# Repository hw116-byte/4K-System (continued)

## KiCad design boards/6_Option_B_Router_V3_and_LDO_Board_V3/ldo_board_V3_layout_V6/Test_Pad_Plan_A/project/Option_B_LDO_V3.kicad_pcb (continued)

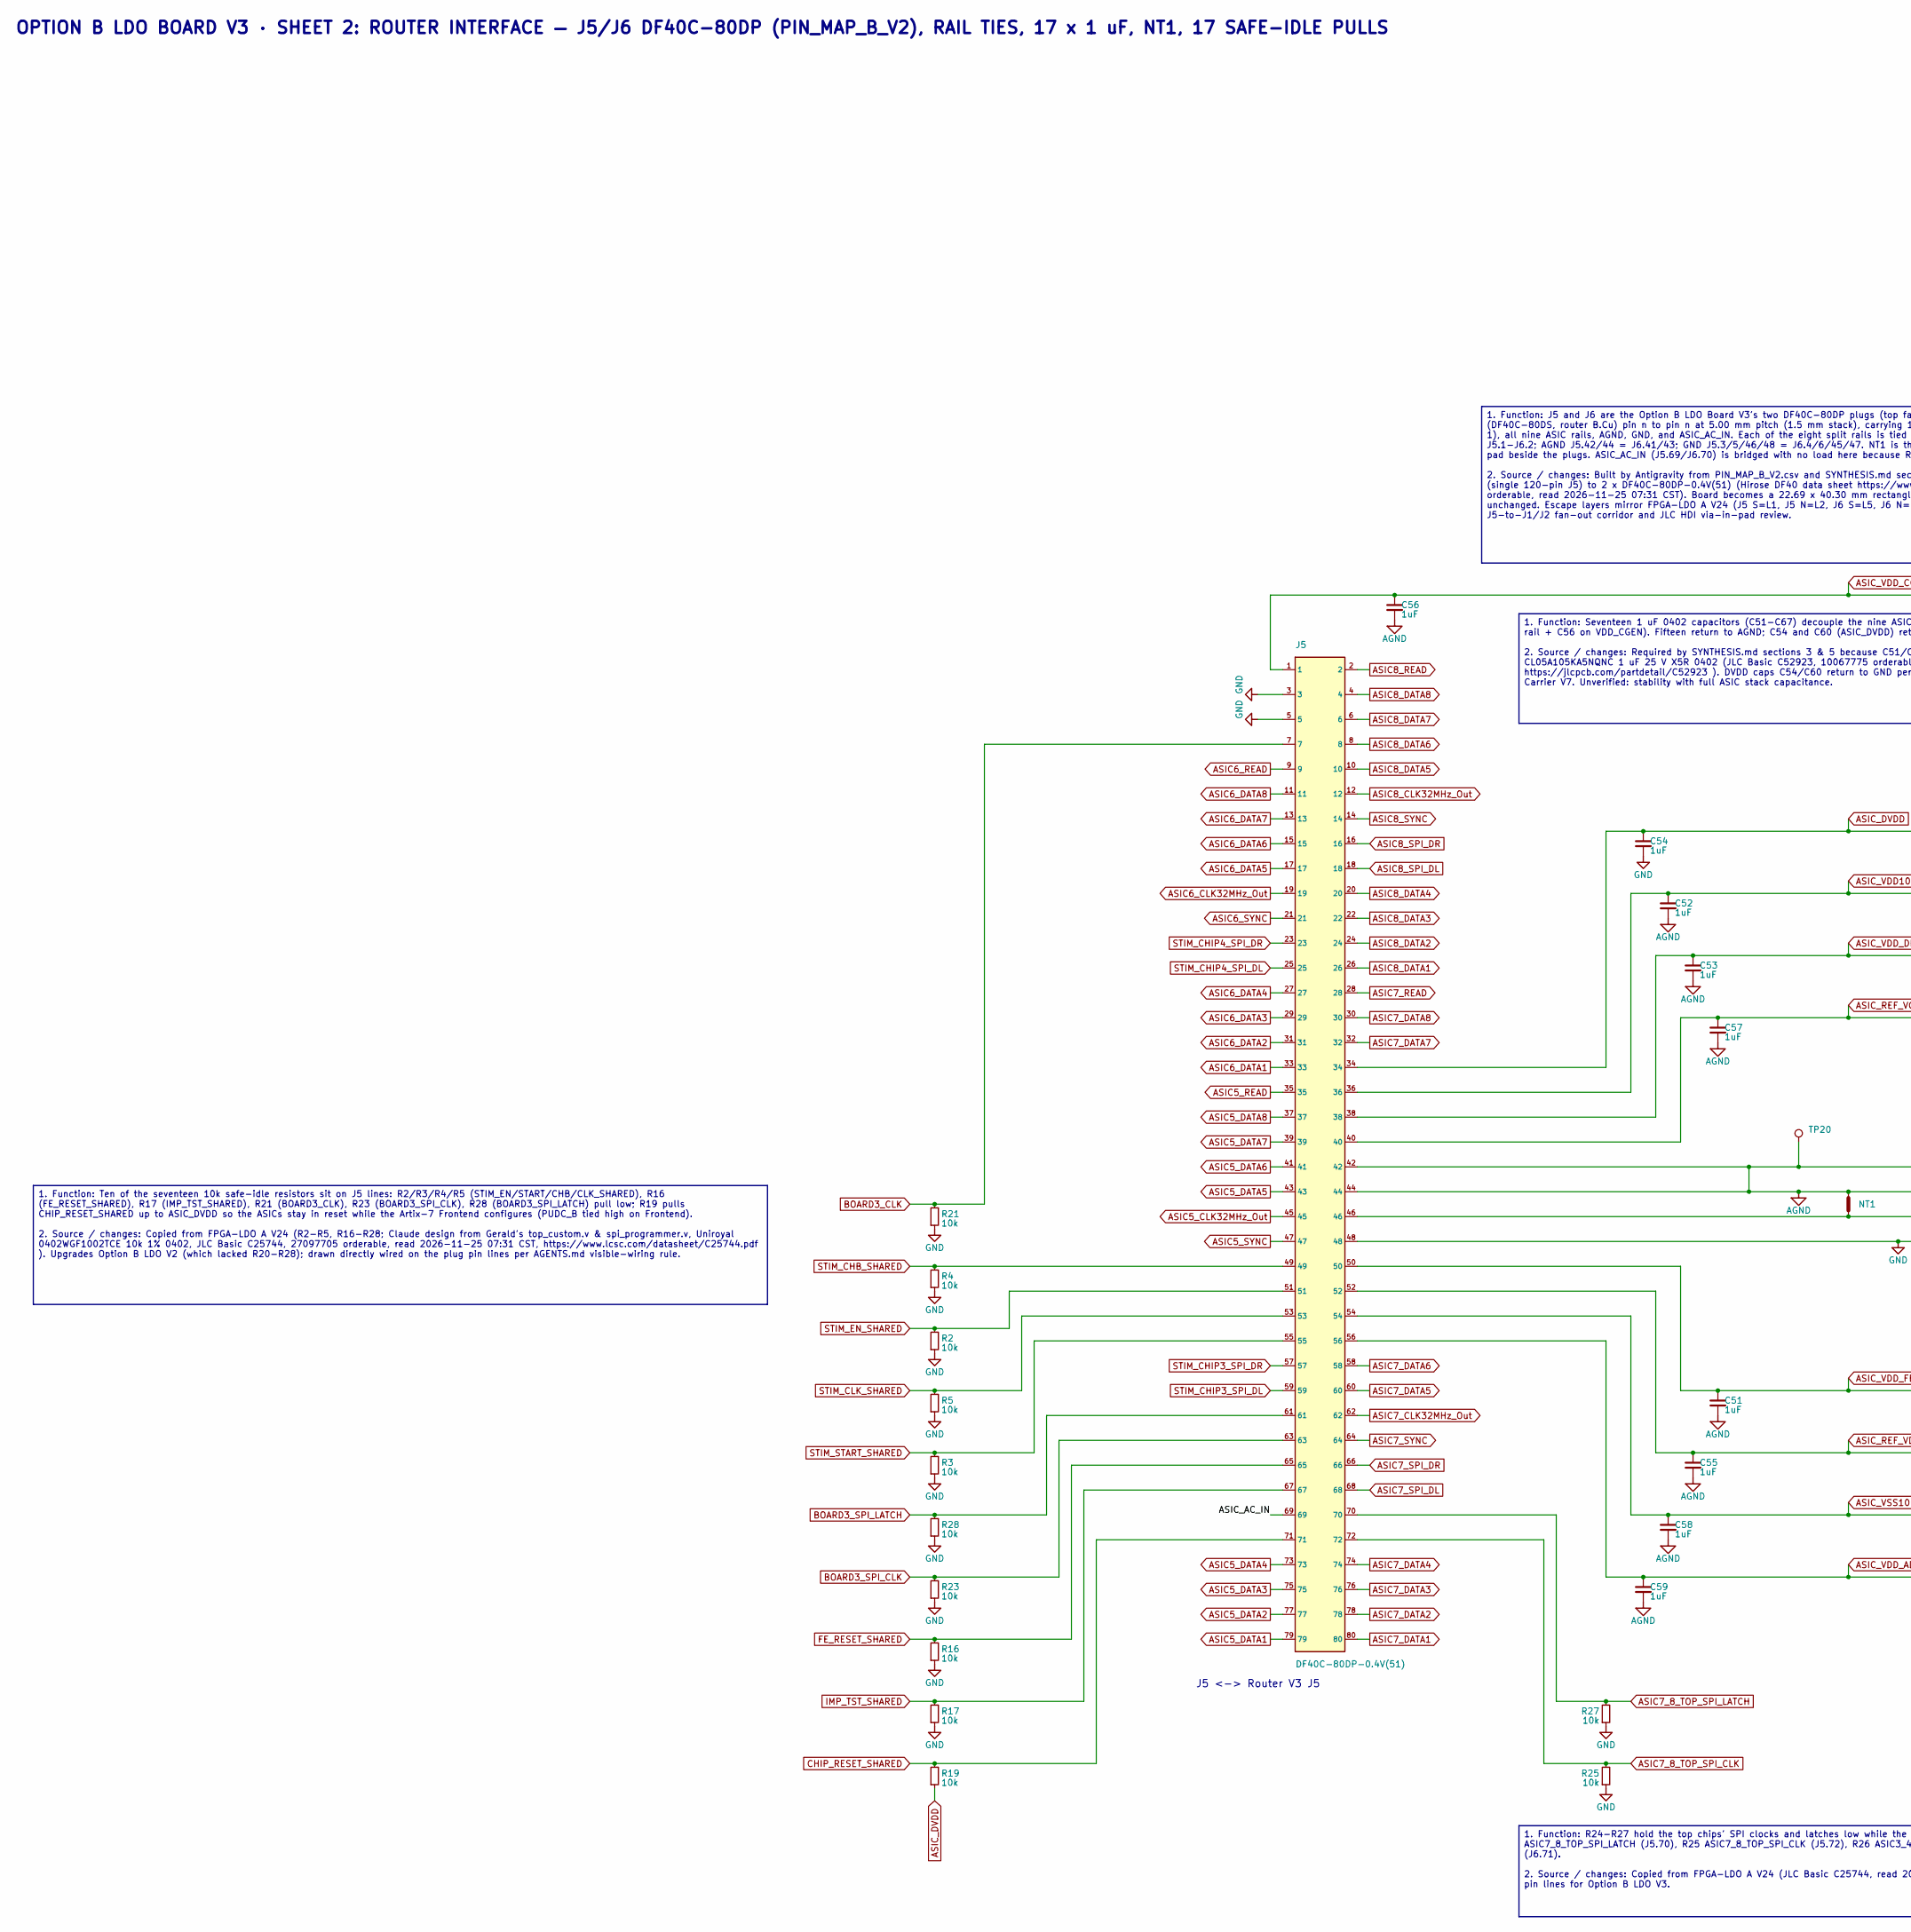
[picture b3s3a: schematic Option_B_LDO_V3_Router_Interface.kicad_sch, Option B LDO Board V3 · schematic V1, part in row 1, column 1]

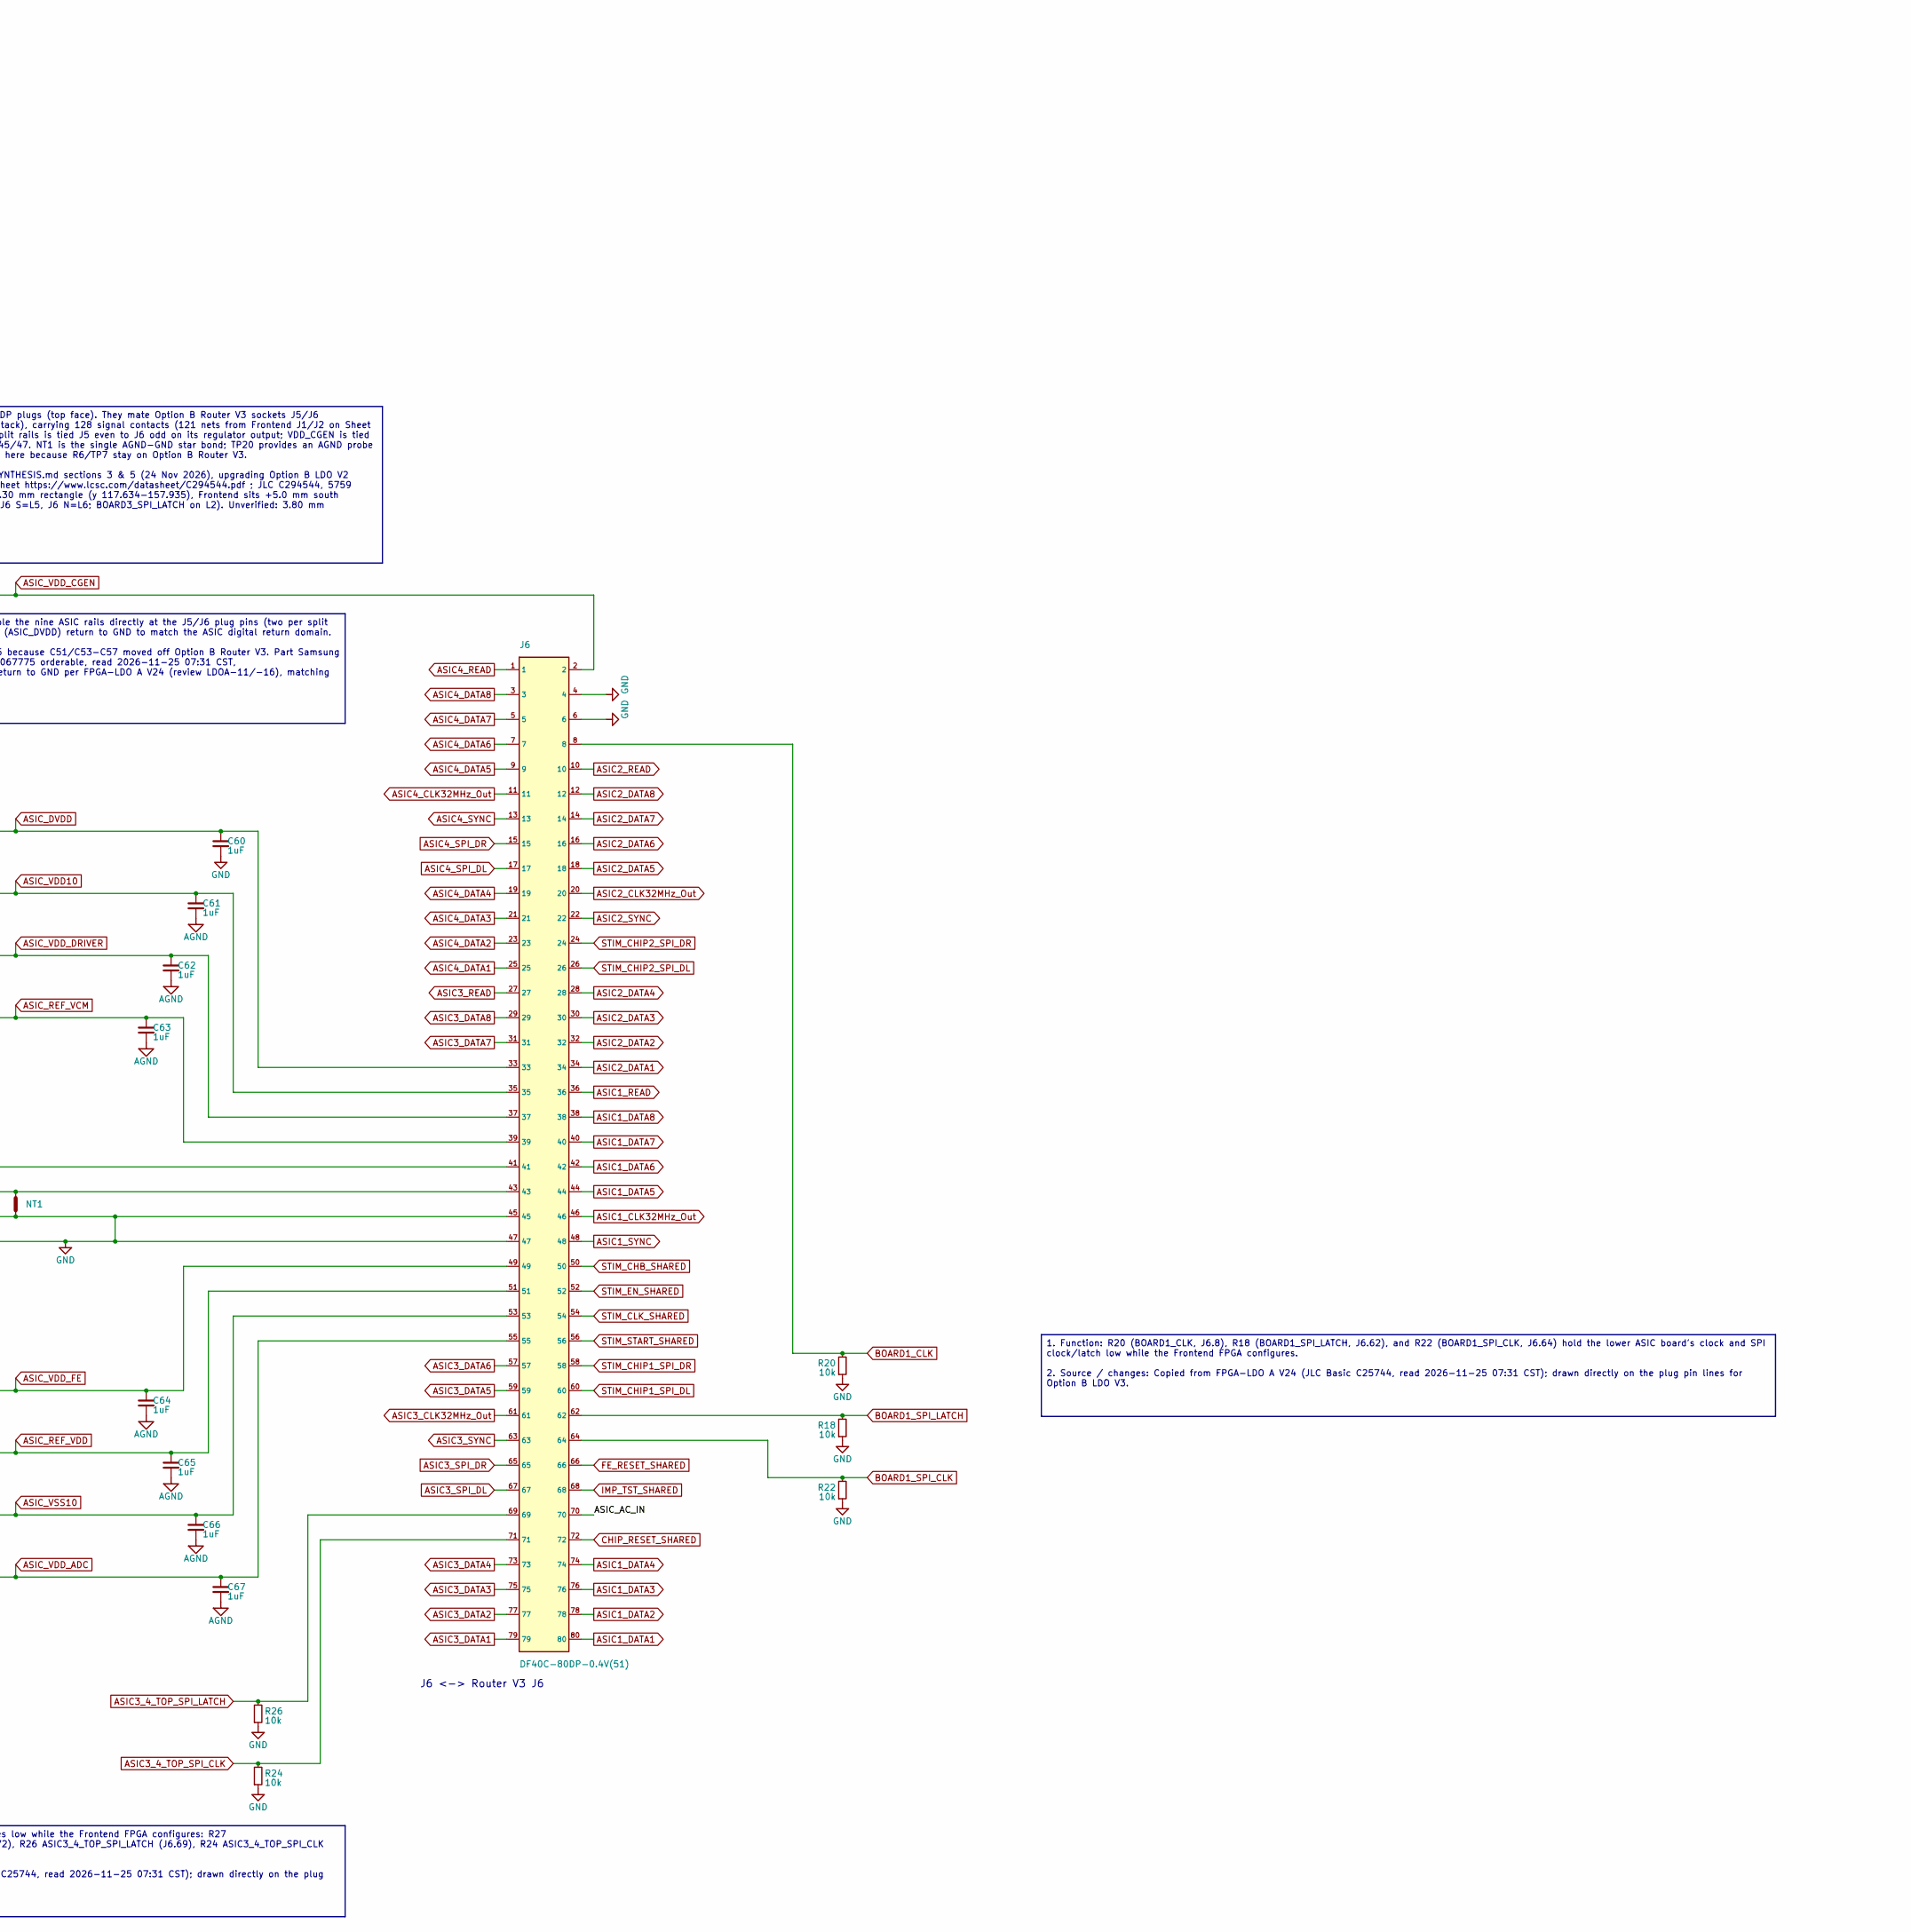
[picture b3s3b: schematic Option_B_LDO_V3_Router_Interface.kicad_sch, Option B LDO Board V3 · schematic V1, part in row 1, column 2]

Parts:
C51, C52, C53, C54, C55, C56, C57, C58, C59, C60, C61, C62, C63, C64, C65, C66, C67: 1uF; C_0402_1005Metric; Voltage 25V; MPN Samsung CL05A105KA5NQNC (1 uF 25 V X5R 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; LCSC C52923
J5, J6: DF40C-80DP-0.4V(51); Hirose_DF40C-80DP-0.4V_2x40-1MP_P0.4mm; MPN DF40C-80DP-0.4V(51); LCSC C294544
NT1: NetTie_2; NetTie-2_SMD_Pad0.5mm
R2, R3, R4, R5, R16, R17, R18, R19, R20, R21, R22, R23, R24, R25, R26, R27, R28: 10k; R_0402_1005Metric; MPN Uniroyal 0402WGF1002TCE (10k 1% 0402); LCSC C25744
TP20: AGND; TestPoint_Pad_D1.0mm_Compact

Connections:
/Router_Interface/ASIC_AC_IN: J5.69, J6.70
AGND: C51.2, C52.2, C53.2, C55.2, C56.2, C57.2, C58.2, C59.2, C61.2, C62.2, C63.2, C64.2, C65.2, C66.2, C67.2, J5.42, J5.44, J6.41, J6.43, NT1.2, TP20.1; also elsewhere on the board
ASIC1_CLK32MHz_Out: J6.46; also elsewhere on the board
ASIC1_DATA1: J6.80; also elsewhere on the board
ASIC1_DATA2: J6.78; also elsewhere on the board
ASIC1_DATA3: J6.76; also elsewhere on the board
ASIC1_DATA4: J6.74; also elsewhere on the board
ASIC1_DATA5: J6.44; also elsewhere on the board
ASIC1_DATA6: J6.42; also elsewhere on the board
ASIC1_DATA7: J6.40; also elsewhere on the board
ASIC1_DATA8: J6.38; also elsewhere on the board
ASIC1_READ: J6.36; also elsewhere on the board
ASIC1_SYNC: J6.48; also elsewhere on the board
ASIC2_CLK32MHz_Out: J6.20; also elsewhere on the board
ASIC2_DATA1: J6.34; also elsewhere on the board
ASIC2_DATA2: J6.32; also elsewhere on the board
ASIC2_DATA3: J6.30; also elsewhere on the board
ASIC2_DATA4: J6.28; also elsewhere on the board
ASIC2_DATA5: J6.18; also elsewhere on the board
ASIC2_DATA6: J6.16; also elsewhere on the board
ASIC2_DATA7: J6.14; also elsewhere on the board
ASIC2_DATA8: J6.12; also elsewhere on the board
ASIC2_READ: J6.10; also elsewhere on the board
ASIC2_SYNC: J6.22; also elsewhere on the board
ASIC3_4_TOP_SPI_CLK: J6.71, R24.1; also elsewhere on the board
ASIC3_4_TOP_SPI_LATCH: J6.69, R26.1; also elsewhere on the board
ASIC3_CLK32MHz_Out: J6.61; also elsewhere on the board
ASIC3_DATA1: J6.79; also elsewhere on the board
ASIC3_DATA2: J6.77; also elsewhere on the board
ASIC3_DATA3: J6.75; also elsewhere on the board
ASIC3_DATA4: J6.73; also elsewhere on the board
ASIC3_DATA5: J6.59; also elsewhere on the board
ASIC3_DATA6: J6.57; also elsewhere on the board
ASIC3_DATA7: J6.31; also elsewhere on the board
ASIC3_DATA8: J6.29; also elsewhere on the board
ASIC3_READ: J6.27; also elsewhere on the board
ASIC3_SPI_DL: J6.67; also elsewhere on the board
ASIC3_SPI_DR: J6.65; also elsewhere on the board
ASIC3_SYNC: J6.63; also elsewhere on the board
ASIC4_CLK32MHz_Out: J6.11; also elsewhere on the board
ASIC4_DATA1: J6.25; also elsewhere on the board
ASIC4_DATA2: J6.23; also elsewhere on the board
ASIC4_DATA3: J6.21; also elsewhere on the board
ASIC4_DATA4: J6.19; also elsewhere on the board
ASIC4_DATA5: J6.9; also elsewhere on the board
ASIC4_DATA6: J6.7; also elsewhere on the board
ASIC4_DATA7: J6.5; also elsewhere on the board
ASIC4_DATA8: J6.3; also elsewhere on the board
ASIC4_READ: J6.1; also elsewhere on the board
ASIC4_SPI_DL: J6.17; also elsewhere on the board
ASIC4_SPI_DR: J6.15; also elsewhere on the board
ASIC4_SYNC: J6.13; also elsewhere on the board
ASIC5_CLK32MHz_Out: J5.45; also elsewhere on the board
ASIC5_DATA1: J5.79; also elsewhere on the board
ASIC5_DATA2: J5.77; also elsewhere on the board
ASIC5_DATA3: J5.75; also elsewhere on the board
ASIC5_DATA4: J5.73; also elsewhere on the board
ASIC5_DATA5: J5.43; also elsewhere on the board
ASIC5_DATA6: J5.41; also elsewhere on the board
ASIC5_DATA7: J5.39; also elsewhere on the board
ASIC5_DATA8: J5.37; also elsewhere on the board
ASIC5_READ: J5.35; also elsewhere on the board
ASIC5_SYNC: J5.47; also elsewhere on the board
ASIC6_CLK32MHz_Out: J5.19; also elsewhere on the board
ASIC6_DATA1: J5.33; also elsewhere on the board
ASIC6_DATA2: J5.31; also elsewhere on the board
ASIC6_DATA3: J5.29; also elsewhere on the board
ASIC6_DATA4: J5.27; also elsewhere on the board
ASIC6_DATA5: J5.17; also elsewhere on the board
ASIC6_DATA6: J5.15; also elsewhere on the board
ASIC6_DATA7: J5.13; also elsewhere on the board
ASIC6_DATA8: J5.11; also elsewhere on the board
ASIC6_READ: J5.9; also elsewhere on the board
ASIC6_SYNC: J5.21; also elsewhere on the board
ASIC7_8_TOP_SPI_CLK: J5.72, R25.1; also elsewhere on the board
ASIC7_8_TOP_SPI_LATCH: J5.70, R27.1; also elsewhere on the board
ASIC7_CLK32MHz_Out: J5.62; also elsewhere on the board
ASIC7_DATA1: J5.80; also elsewhere on the board
ASIC7_DATA2: J5.78; also elsewhere on the board
ASIC7_DATA3: J5.76; also elsewhere on the board
ASIC7_DATA4: J5.74; also elsewhere on the board
ASIC7_DATA5: J5.60; also elsewhere on the board
ASIC7_DATA6: J5.58; also elsewhere on the board
ASIC7_DATA7: J5.32; also elsewhere on the board
ASIC7_DATA8: J5.30; also elsewhere on the board
ASIC7_READ: J5.28; also elsewhere on the board
ASIC7_SPI_DL: J5.68; also elsewhere on the board
ASIC7_SPI_DR: J5.66; also elsewhere on the board
ASIC7_SYNC: J5.64; also elsewhere on the board
ASIC8_CLK32MHz_Out: J5.12; also elsewhere on the board
ASIC8_DATA1: J5.26; also elsewhere on the board
ASIC8_DATA2: J5.24; also elsewhere on the board
ASIC8_DATA3: J5.22; also elsewhere on the board
ASIC8_DATA4: J5.20; also elsewhere on the board
ASIC8_DATA5: J5.10; also elsewhere on the board
ASIC8_DATA6: J5.8; also elsewhere on the board
ASIC8_DATA7: J5.6; also elsewhere on the board
ASIC8_DATA8: J5.4; also elsewhere on the board
ASIC8_READ: J5.2; also elsewhere on the board
ASIC8_SPI_DL: J5.18; also elsewhere on the board
ASIC8_SPI_DR: J5.16; also elsewhere on the board
ASIC8_SYNC: J5.14; also elsewhere on the board
ASIC_DVDD: C54.1, C60.1, J5.34, J6.33, R19.2; also elsewhere on the board
ASIC_REF_VCM: C57.1, C63.1, J5.40, J6.39; also elsewhere on the board
ASIC_REF_VDD: C55.1, C65.1, J5.52, J6.51; also elsewhere on the board
ASIC_VDD10: C52.1, C61.1, J5.36, J6.35; also elsewhere on the board
ASIC_VDD_ADC: C59.1, C67.1, J5.56, J6.55; also elsewhere on the board
ASIC_VDD_CGEN: C56.1, J5.1, J6.2; also elsewhere on the board
ASIC_VDD_DRIVER: C53.1, C62.1, J5.38, J6.37; also elsewhere on the board
ASIC_VDD_FE: C51.1, C64.1, J5.50, J6.49; also elsewhere on the board
ASIC_VSS10: C58.1, C66.1, J5.54, J6.53; also elsewhere on the board
BOARD1_CLK: J6.8, R20.1; also elsewhere on the board
BOARD1_SPI_CLK: J6.64, R22.1; also elsewhere on the board
BOARD1_SPI_LATCH: J6.62, R18.1; also elsewhere on the board
BOARD3_CLK: J5.7, R21.1; also elsewhere on the board
BOARD3_SPI_CLK: J5.63, R23.1; also elsewhere on the board
BOARD3_SPI_LATCH: J5.61, R28.1; also elsewhere on the board
CHIP_RESET_SHARED: J5.71, J6.72, R19.1; also elsewhere on the board
FE_RESET_SHARED: J5.65, J6.66, R16.1; also elsewhere on the board
GND: C54.2, C60.2, J5.3, J5.5, J5.46, J5.48, J6.4, J6.6, J6.45, J6.47, NT1.1, R2.2, R3.2, R4.2, R5.2, R16.2, R17.2, R18.2, R20.2, R21.2, R22.2, R23.2, R24.2, R25.2, R26.2, R27.2, R28.2; also elsewhere on the board
IMP_TST_SHARED: J5.67, J6.68, R17.1; also elsewhere on the board
STIM_CHB_SHARED: J5.49, J6.50, R4.1; also elsewhere on the board
STIM_CHIP1_SPI_DL: J6.60; also elsewhere on the board
STIM_CHIP1_SPI_DR: J6.58; also elsewhere on the board
STIM_CHIP2_SPI_DL: J6.26; also elsewhere on the board
STIM_CHIP2_SPI_DR: J6.24; also elsewhere on the board
STIM_CHIP3_SPI_DL: J5.59; also elsewhere on the board
STIM_CHIP3_SPI_DR: J5.57; also elsewhere on the board
STIM_CHIP4_SPI_DL: J5.25; also elsewhere on the board
STIM_CHIP4_SPI_DR: J5.23; also elsewhere on the board
STIM_CLK_SHARED: J5.53, J6.54, R5.1; also elsewhere on the board
STIM_EN_SHARED: J5.51, J6.52, R2.1; also elsewhere on the board
STIM_START_SHARED: J5.55, J6.56, R3.1; also elsewhere on the board

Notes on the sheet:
1. Function: J5 and J6 are the Option B LDO Board V3's two DF40C-80DP plugs (top face). They mate Option B Router V3 sockets J5/J6 (DF40C-80DS, router B.Cu) pin n to pin n at 5.00 mm pitch (1.5 mm stack), carrying 128 signal contacts (121 nets from Frontend J1/J2 on Sheet 1), all nine ASIC rails, A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
1. Function: Seventeen 1 uF 0402 capacitors (C51-C67) decouple the nine ASIC rails directly at the J5/J6 plug pins (two per split rail + C56 on VDD_CGEN). Fifteen return to AGND; C54 and C60 (ASIC_DVDD) return to GND to match the ASIC digital return domain. 2. Source / changes: Required by SYNTHESI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
1. Function: Ten of the seventeen 10k safe-idle resistors sit on J5 lines: R2/R3/R4/R5 (STIM_EN/START/CHB/CLK_SHARED), R16 (FE_RESET_SHARED), R17 (IMP_TST_SHARED), R21 (BOARD3_CLK), R23 (BOARD3_SPI_CLK), R28 (BOARD3_SPI_LATCH) pull low; R19 pulls CHIP_RESET_SHARED up to ASIC_DVDD so the ASICs stay 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
1. Function: R24-R27 hold the top chips' SPI clocks and latches low while the Frontend FPGA configures: R27 ASIC7_8_TOP_SPI_LATCH (J5.70), R25 ASIC7_8_TOP_SPI_CLK (J5.72), R26 ASIC3_4_TOP_SPI_LATCH (J6.69), R24 ASIC3_4_TOP_SPI_CLK (J6.71). 2. Source / changes: Copied from FPGA-LDO A V24 (JLC Basic 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
1. Function: R20 (BOARD1_CLK, J6.8), R18 (BOARD1_SPI_LATCH, J6.62), and R22 (BOARD1_SPI_CLK, J6.64) hold the lower ASIC board's clock and SPI clock/latch low while the Frontend FPGA configures. 2. Source / changes: Copied from FPGA-LDO A V24 (JLC Basic C25744, read 2026-11-25 07:31 CST); drawn dire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
OPTION B LDO BOARD V3 · SHEET 2: ROUTER INTERFACE — J5/J6 DF40C-80DP (PIN_MAP_B_V2), RAIL TIES, 17 x 1 uF, NT1, 17 SAFE-IDLE PULLS
J5 <-> Router V3 J5
J6 <-> Router V3 J6

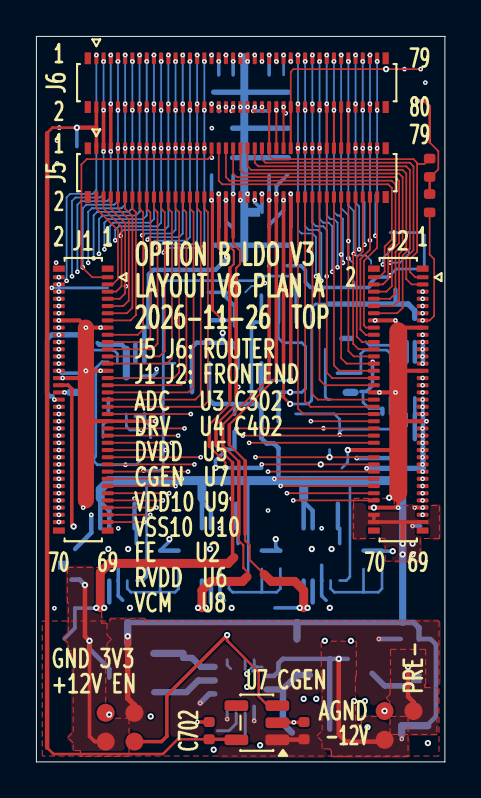
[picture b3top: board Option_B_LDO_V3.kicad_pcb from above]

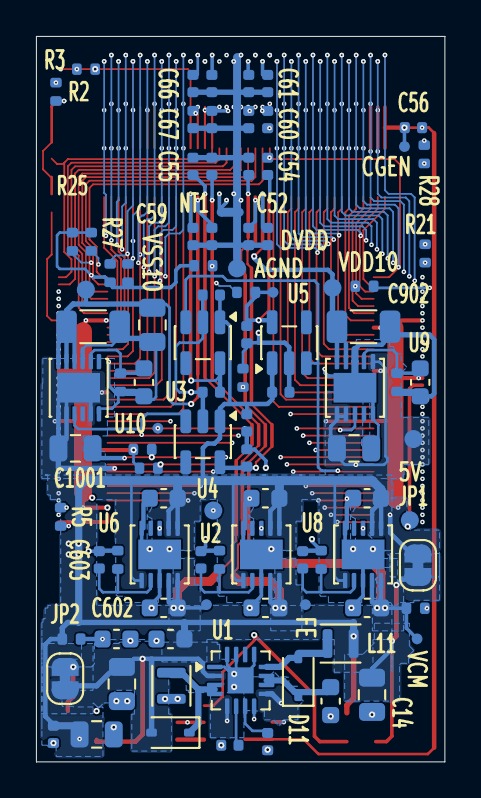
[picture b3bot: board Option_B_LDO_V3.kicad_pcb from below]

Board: 6 copper layers, 22.7 x 40.3 mm, 114 parts (98 on the bottom side), 150 nets.
